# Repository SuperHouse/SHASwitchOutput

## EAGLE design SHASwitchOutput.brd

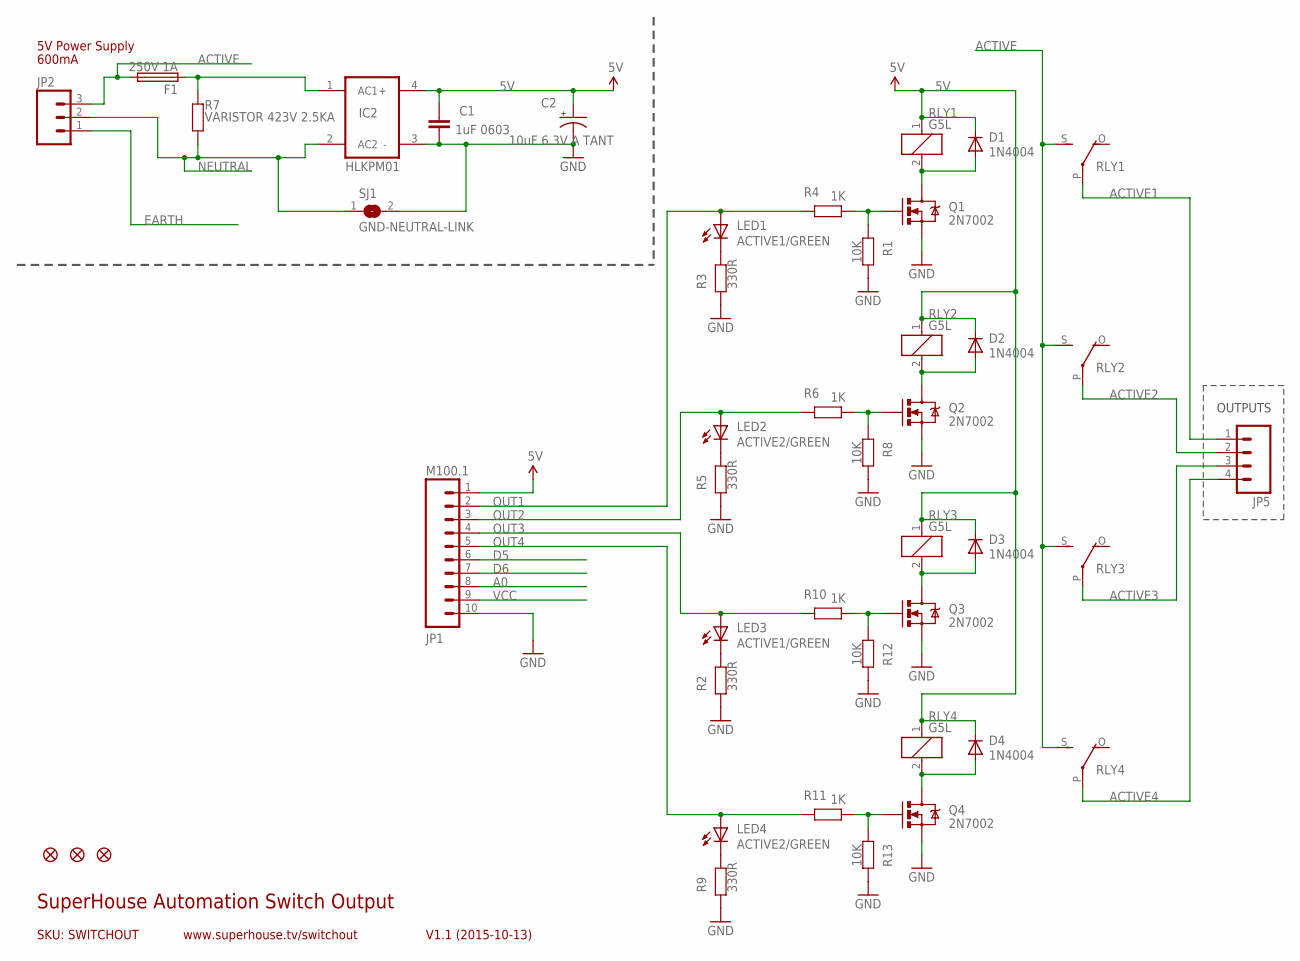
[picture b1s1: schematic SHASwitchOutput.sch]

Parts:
C1: 1uF 0603; 0603@1
C2: 10uF 6.3V A TANT; EIA3216
D1, D2, D3, D4: 1N4004; SMB-DIODE
F1: 250V 1A; PICOFUSE-V
FID1, FID2, FID3: FIDUCIAL1X2.5; FIDUCIAL-1X2.5
IC2: HLKPM01
JP1: M100.1; 1X10
JP2: M035MM; SCREWTERMINAL-5MM-3
JP5: M045MM; SCREWTERMINAL-5MM-4
LED1, LED3: ACTIVE1/GREEN; LED-0603
LED2, LED4: ACTIVE2/GREEN; LED-0603
Q1, Q2, Q3, Q4: 2N7002; SOT23-3
R1, R8, R12, R13: 10K; 0603
R2, R3, R5, R9: 330R; 0603
R4, R6, R10, R11: 1K; 0603
R7: VARISTOR 423V 2.5KA; AXIAL-0.3
RLY1, RLY2, RLY3, RLY4: G5L; G5LE
SJ1: GND-NEUTRAL-LINK; SJ

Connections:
5V: C1.1, C2.A (+), D1.C, D2.C, D3.C, D4.C, IC2.4 (+), JP1.1, RLY1.1, RLY2.1, RLY3.1, RLY4.1
$N16: F1.1, IC2.1 (AC1), R7.P$2 (2)
A0: JP1.8
ACTIVE: F1.2, JP2.3, RLY1.S, RLY2.S, RLY3.S, RLY4.S
ACTIVE1: JP5.1, RLY1.P
ACTIVE2: JP5.2, RLY2.P
ACTIVE3: JP5.3, RLY3.P
ACTIVE4: JP5.4, RLY4.P
D5: JP1.6
D6: JP1.7
EARTH: JP2.1
GND: C1.2, C2.C (-), IC2.3 (-), JP1.10, Q1.2 (S), Q2.2 (S), Q3.2 (S), Q4.2 (S), R1.2, R2.1, R3.1, R5.1, R8.2, R9.1, R12.2, R13.2, SJ1.2
unnamed: LED3.C, R2.2
unnamed: LED2.C, R5.2
unnamed: D2.A, Q2.3 (D), RLY2.2
unnamed: D1.A, Q1.3 (D), RLY1.2
unnamed: Q1.1 (G), R1.1, R4.1
unnamed: Q2.1 (G), R6.1, R8.1
unnamed: LED4.C, R9.2
unnamed: D4.A, Q4.3 (D), RLY4.2
unnamed: D3.A, Q3.3 (D), RLY3.2
unnamed: Q3.1 (G), R10.1, R12.1
unnamed: Q4.1 (G), R11.1, R13.1
unnamed: LED1.C, R3.2
NEUTRAL: IC2.2 (AC2), JP2.2, R7.P$1 (1), SJ1.1
OUT1: JP1.2, LED1.A, R4.2
OUT2: JP1.3, LED2.A, R6.2
OUT3: JP1.4, LED3.A, R10.2
OUT4: JP1.5, LED4.A, R11.2
VCC: JP1.9

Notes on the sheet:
SKU: SWITCHOUT
5V Power Supply
600mA
SuperHouse Automation Switch Output
V1.1 (2015-10-13)
www.superhouse.tv/switchout
OUTPUTS

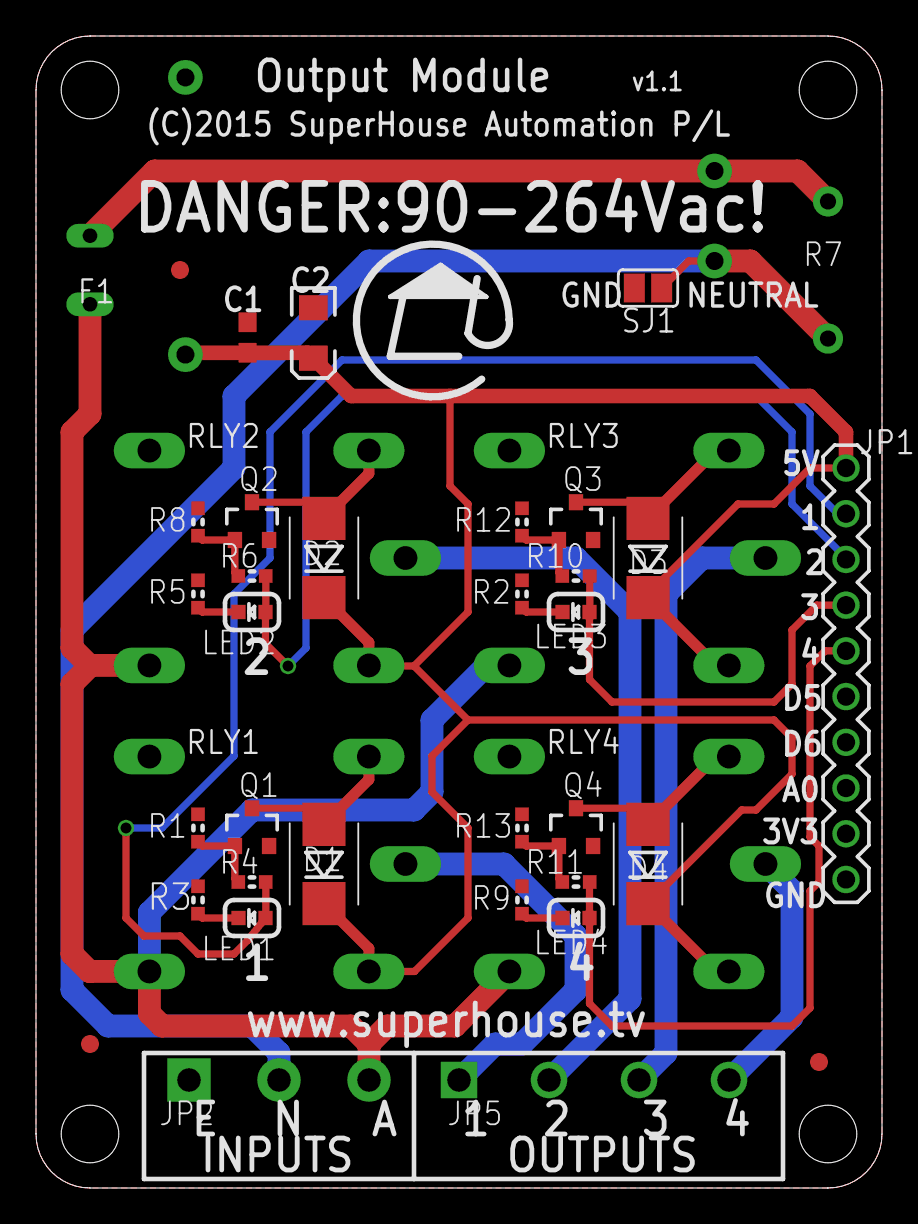
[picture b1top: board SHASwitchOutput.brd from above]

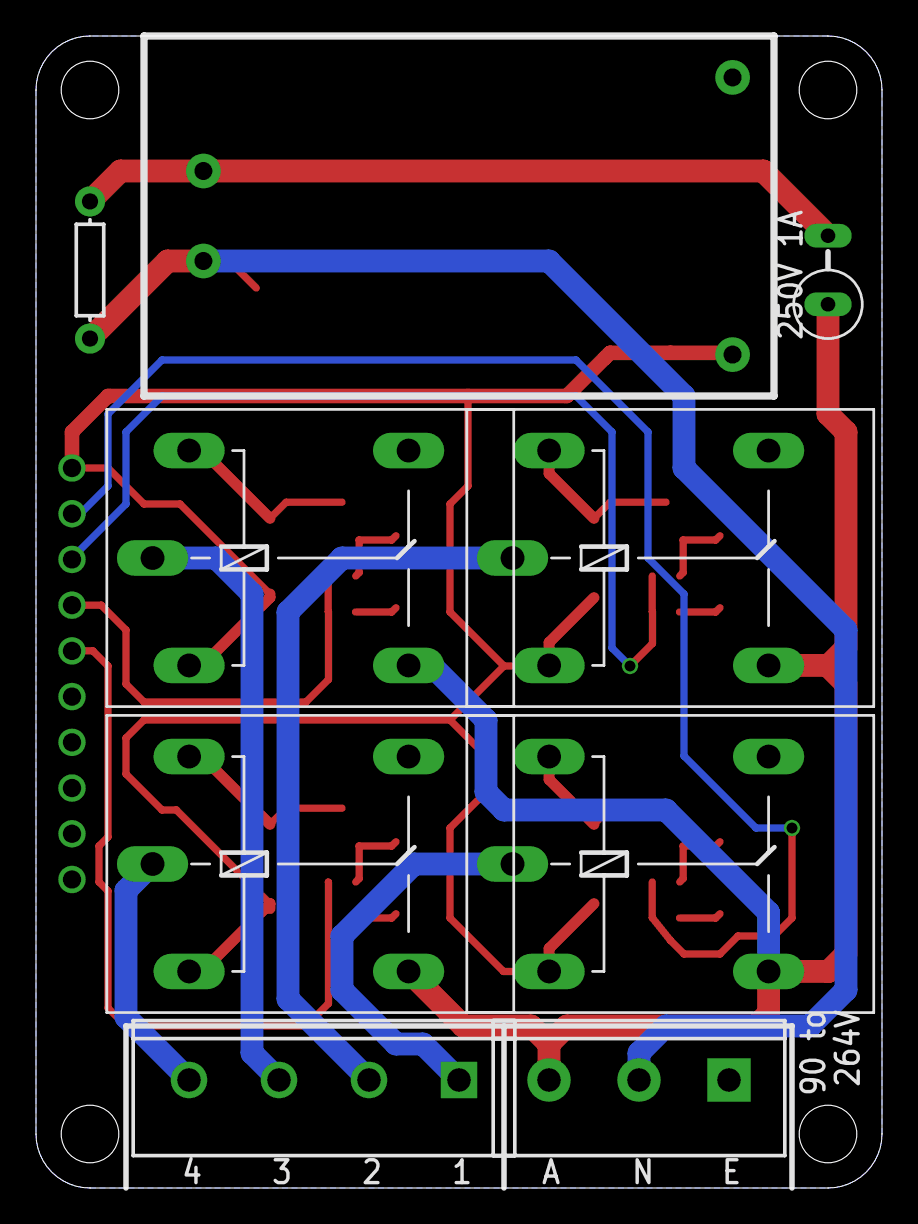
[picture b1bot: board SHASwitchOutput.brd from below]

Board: 2 copper layers, 47.0 x 64.0 mm, 40 parts (9 on the bottom side), 25 nets.

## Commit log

2015-08-18 Initial import for v1.0 release
2015-08-20 Changed screw terminals from 3.5mm pitch to 5mm
2015-08-20 Improved via positions and part name labels
2015-10-13 Added GND-Neutral solder jumper (normally open) Changed fuse to vertial orientation

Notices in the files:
SHASwitchOutput.brd:
(C)2015 SuperHouse Automation P/L
parts and their libraries:
freetronics-original: Licensing: CC v3.0 Share-Alike You are welcome to use this library for commercial purposes.
